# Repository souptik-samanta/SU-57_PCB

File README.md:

This pcb blinks and glows when dark in a shape of SU 57

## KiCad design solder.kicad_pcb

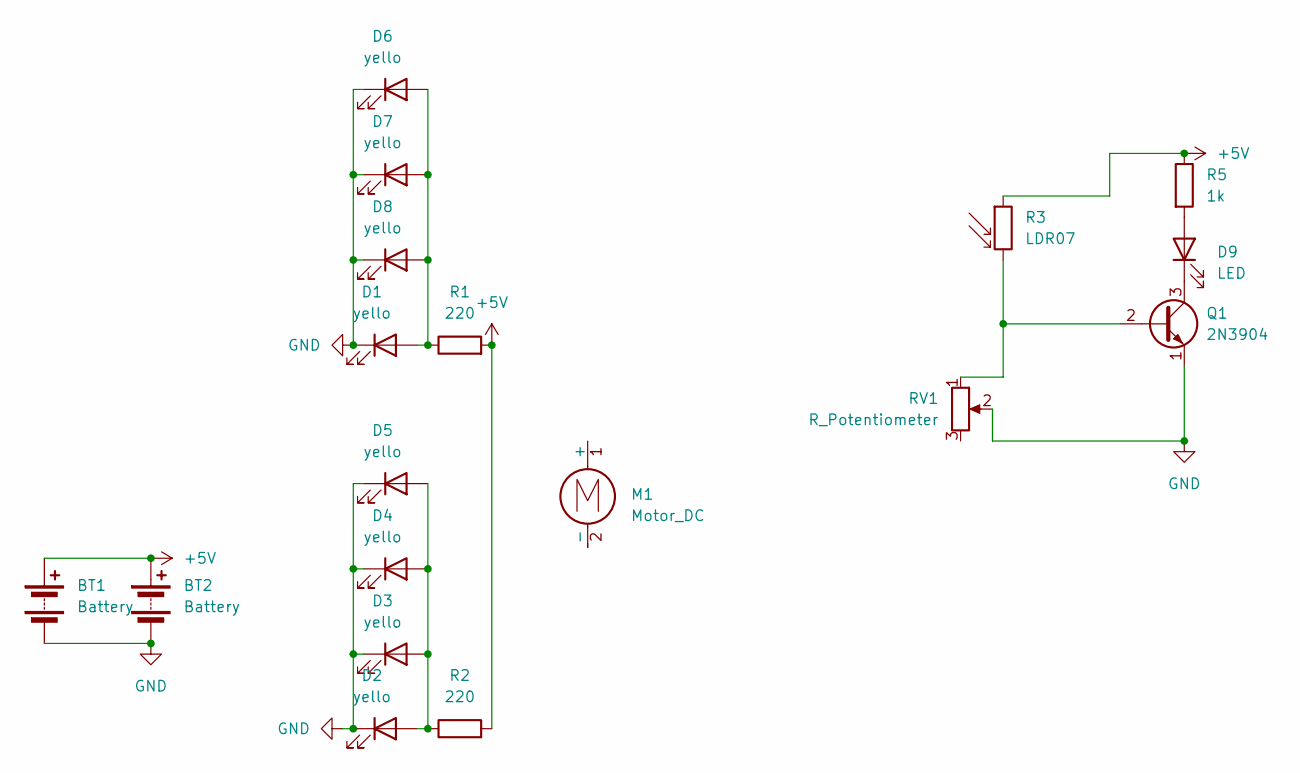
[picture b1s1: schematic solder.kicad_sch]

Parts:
BT1, BT2: Battery; BatteryHolder_Keystone_3034_1x20mm
D1, D2, D3, D4, D5, D6, D7, D8: yello; LED_0805_2012Metric_Pad1.15x1.40mm_HandSolder
D9: LED; LED_D5.0mm
M1: Motor_DC; PinHeader_1x02_P2.54mm_Vertical_SMD_Pin1Right
Q1: 2N3904; TO-92_Inline
R1, R2: 220; C_0805_2012Metric_Pad1.18x1.45mm_HandSolder
R3: LDR07; R_LDR_5.1x4.3mm_P3.4mm_Vertical
R5: 1k; R_Axial_DIN0207_L6.3mm_D2.5mm_P7.62mm_Horizontal
RV1: R_Potentiometer; Potentiometer_ACP_CA9-H5_Horizontal

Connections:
+5V: BT1.1 (+), BT2.1 (+), R1.2, R2.2, R3.1, R5.1
GND: BT1.2 (-), BT2.2 (-), D1.1 (K), D2.1 (K), D3.1 (K), D4.1 (K), D5.1 (K), D6.1 (K), D7.1 (K), D8.1 (K), Q1.1 (E), RV1.2
unnamed: D1.2 (A), D6.2 (A), D7.2 (A), D8.2 (A), R1.1
unnamed: D2.2 (A), D3.2 (A), D4.2 (A), D5.2 (A), R2.1
unnamed: D9.2 (A), R5.2
unnamed: D9.1 (K), Q1.3 (C)
unnamed: Q1.2 (B), R3.2, RV1.1

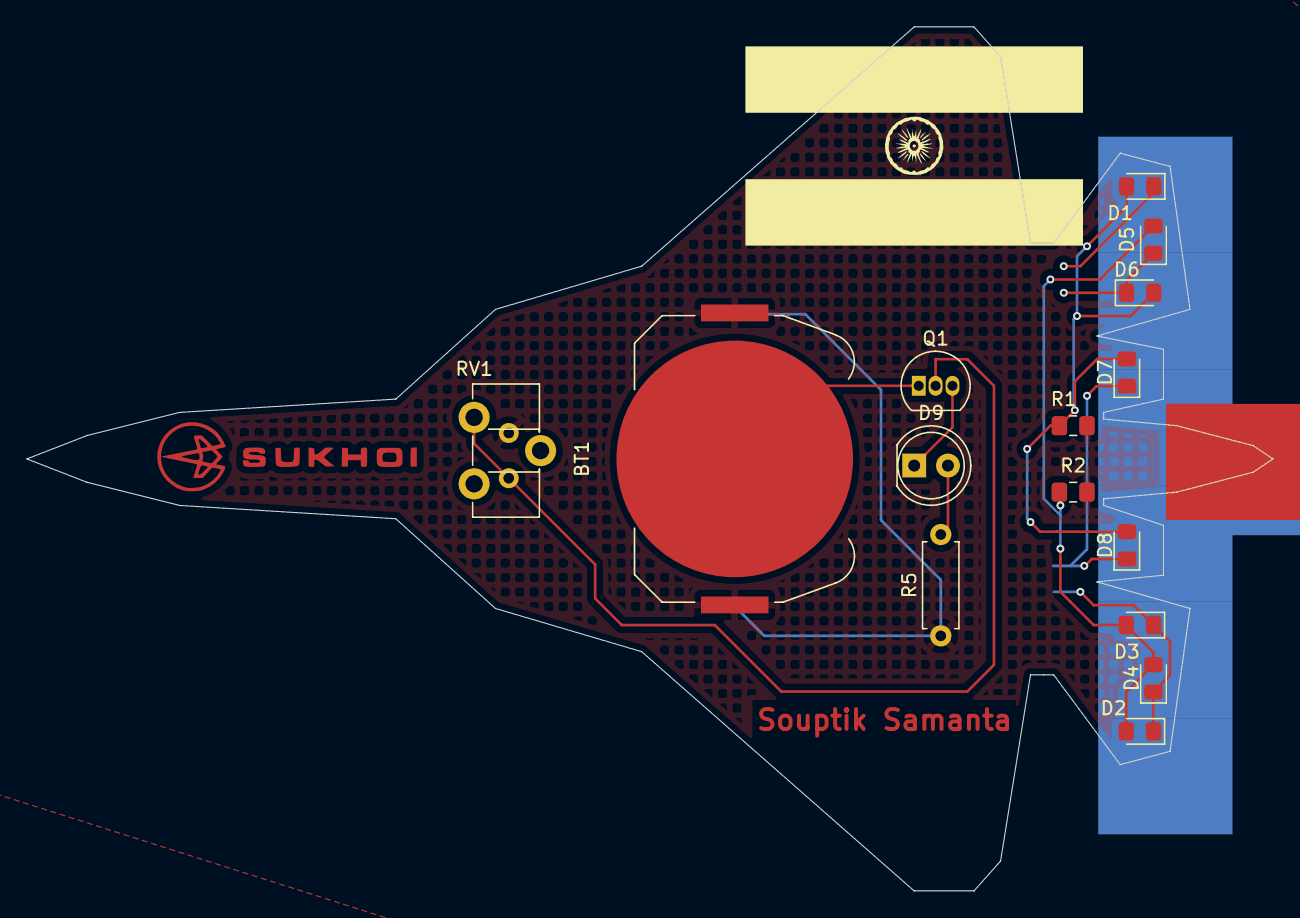
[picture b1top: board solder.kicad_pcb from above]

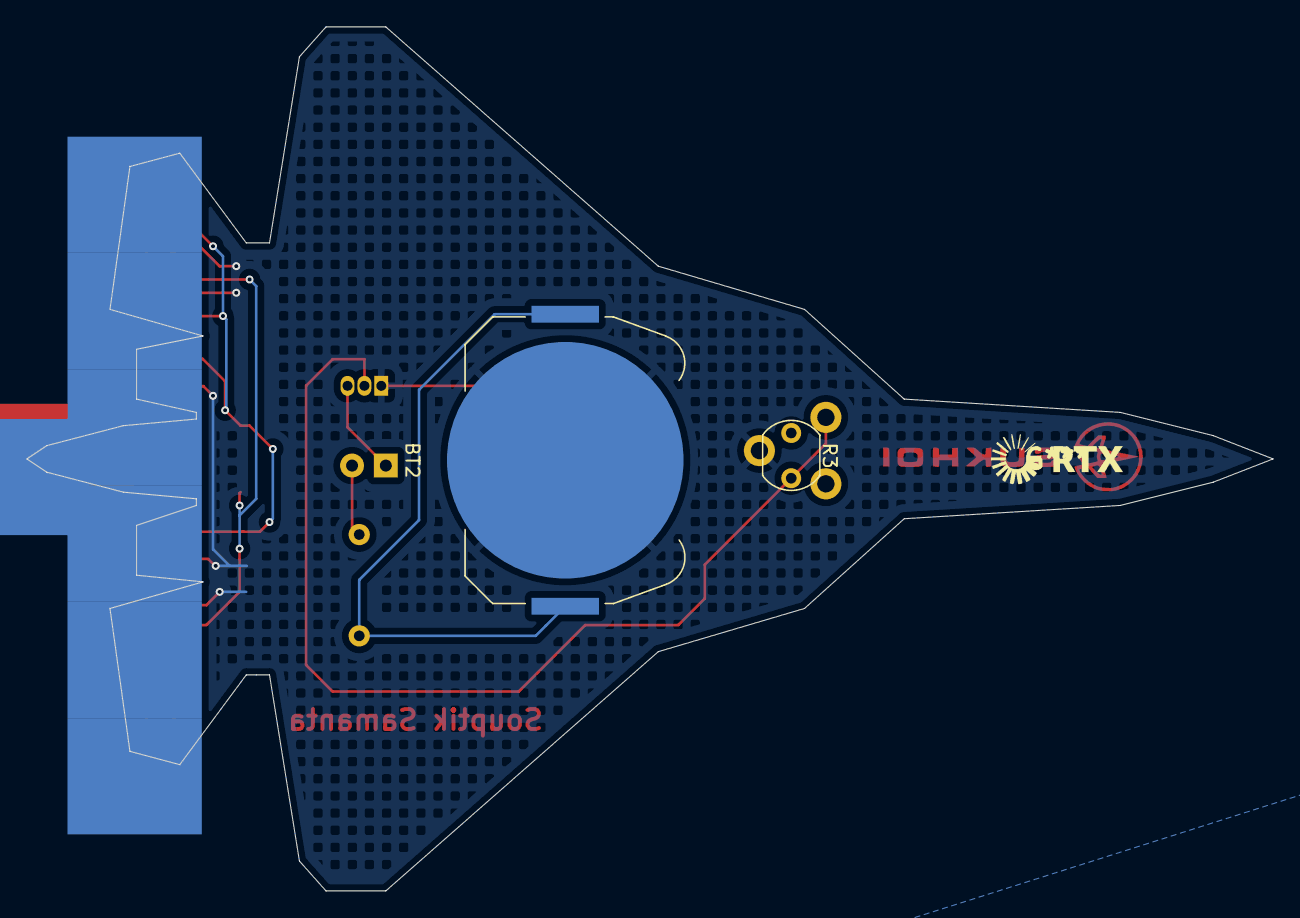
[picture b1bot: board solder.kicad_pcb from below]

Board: 2 copper layers, 93.8 x 65.0 mm, 17 parts (2 on the bottom side), 7 nets.

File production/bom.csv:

Designator,Footprint,Quantity,Value,LCSC Part #
"BT1, BT2",BatteryHolder_Keystone_3034_1x20mm,2,Battery,
"D1, D2, D3, D4, D5, D6, D7, D8",0805,8,yello,
D9,LED_D5.0mm,1,LED,
Q1,TO-92_Inline,1,2N3904,
"R1, R2",0805,2,220,
R3,R_LDR_5.1x4.3mm_P3.4mm_Vertical,1,LDR07,
R5,R_Axial_DIN0207_L6.3mm_D2.5mm_P7.62mm_Horizontal,1,1k,
RV1,Potentiometer_ACP_CA9-H5_Horizontal,1,R_Potentiometer,

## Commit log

2025-05-04 fixed
2025-05-12 pcb and gerber in prod
